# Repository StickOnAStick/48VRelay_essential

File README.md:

Ignore me trying to work with ki-cads git management. Project is located at `RelatBoard/48VRelay/48VERelay`

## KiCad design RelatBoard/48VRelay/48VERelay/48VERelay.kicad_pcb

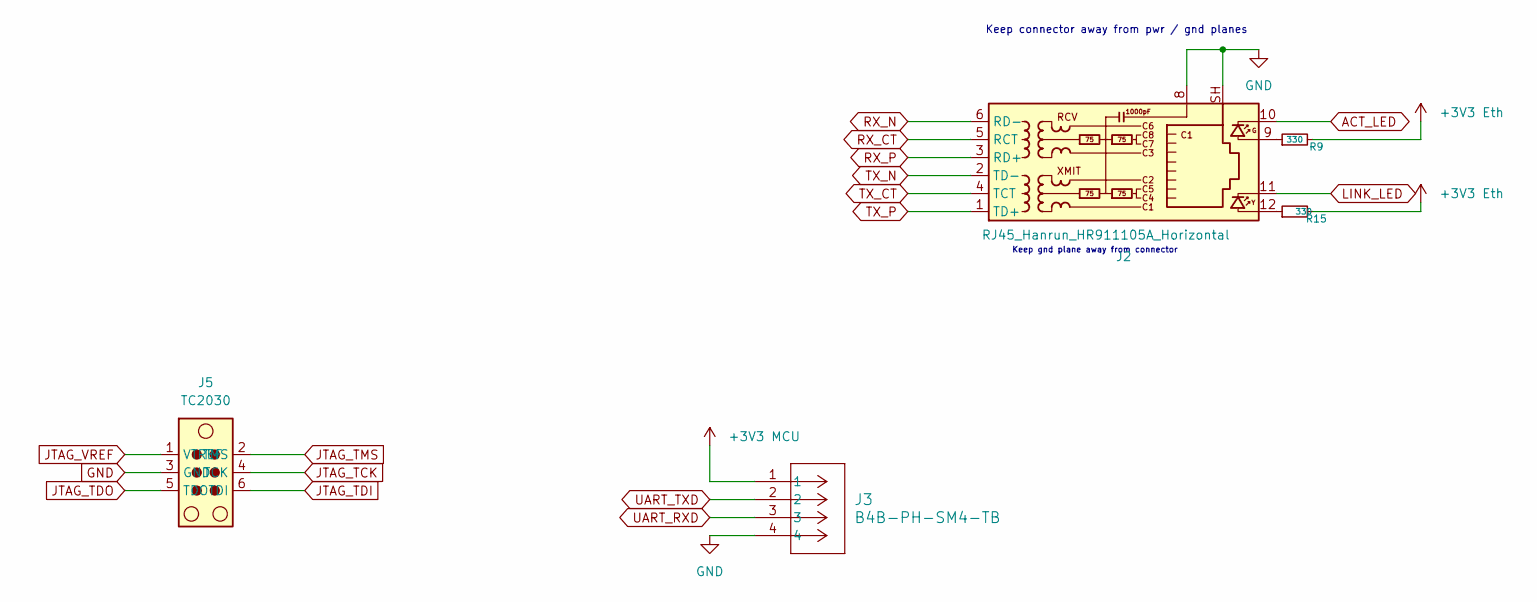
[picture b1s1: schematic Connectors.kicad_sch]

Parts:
J2: RJ45_Hanrun_HR911105A_Horizontal
J3: B4B-PH-SM4-TB; PinHeader_1x04_P2.54mm_Vertical
J5: TC2030; Tag-Connect_TC2030-IDC-NL_2x03_P1.27mm_Vertical
R9, R15: 330; R_0603_1608Metric

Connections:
3V3 MCU: J3.1; also elsewhere on the board
+3V3 Eth: R9.2, R15.2; also elsewhere on the board
ACT_LED: J2.10; also elsewhere on the board
GND: J2.8, J2.SH, J3.4; also elsewhere on the board
LINK_LED: J2.11; also elsewhere on the board
unnamed: J2.9, R9.1
unnamed: J2.12, R15.1
RX_CT: J2.5 (RCT); also elsewhere on the board
RX_N: J2.6 (RD-); also elsewhere on the board
RX_P: J2.3 (RD+); also elsewhere on the board
TX_CT: J2.4 (TCT); also elsewhere on the board
TX_N: J2.2 (TD-); also elsewhere on the board
TX_P: J2.1 (TD+); also elsewhere on the board
UART_RXD: J3.3; also elsewhere on the board
UART_TXD: J3.2; also elsewhere on the board

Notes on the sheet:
Keep gnd plane away from connector
Keep connector away from pwr / gnd planes

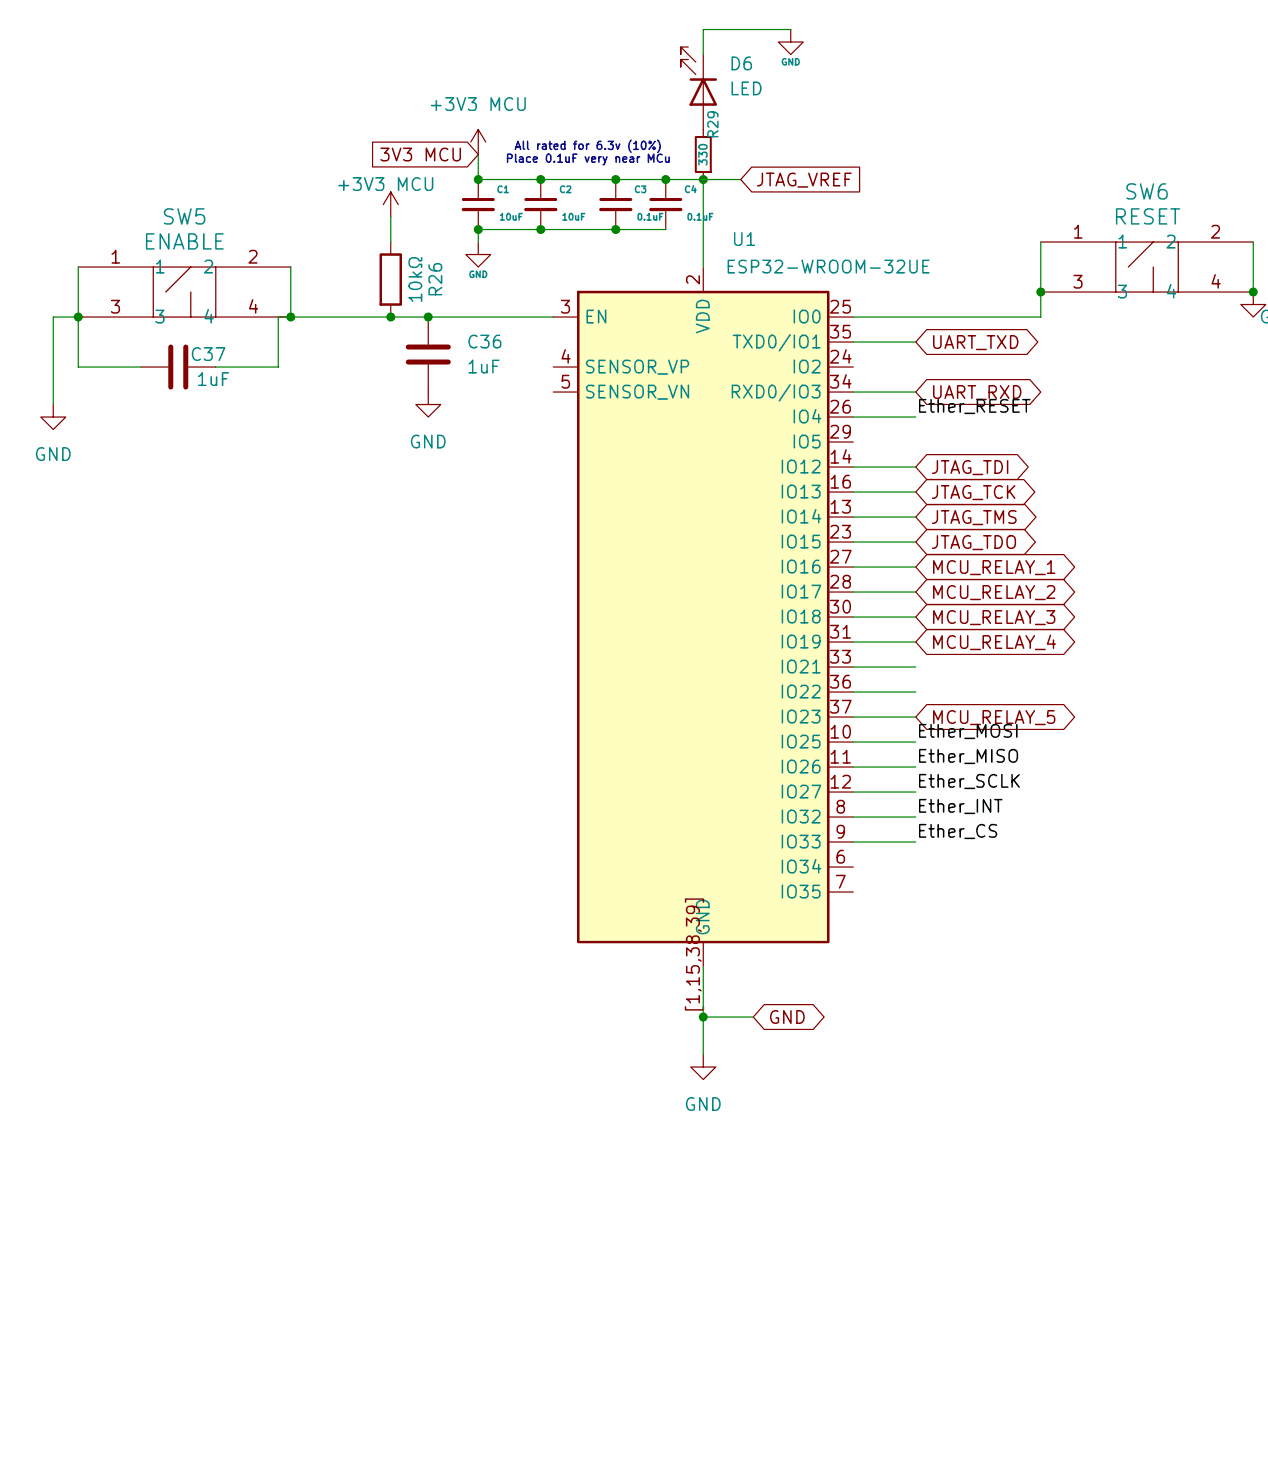
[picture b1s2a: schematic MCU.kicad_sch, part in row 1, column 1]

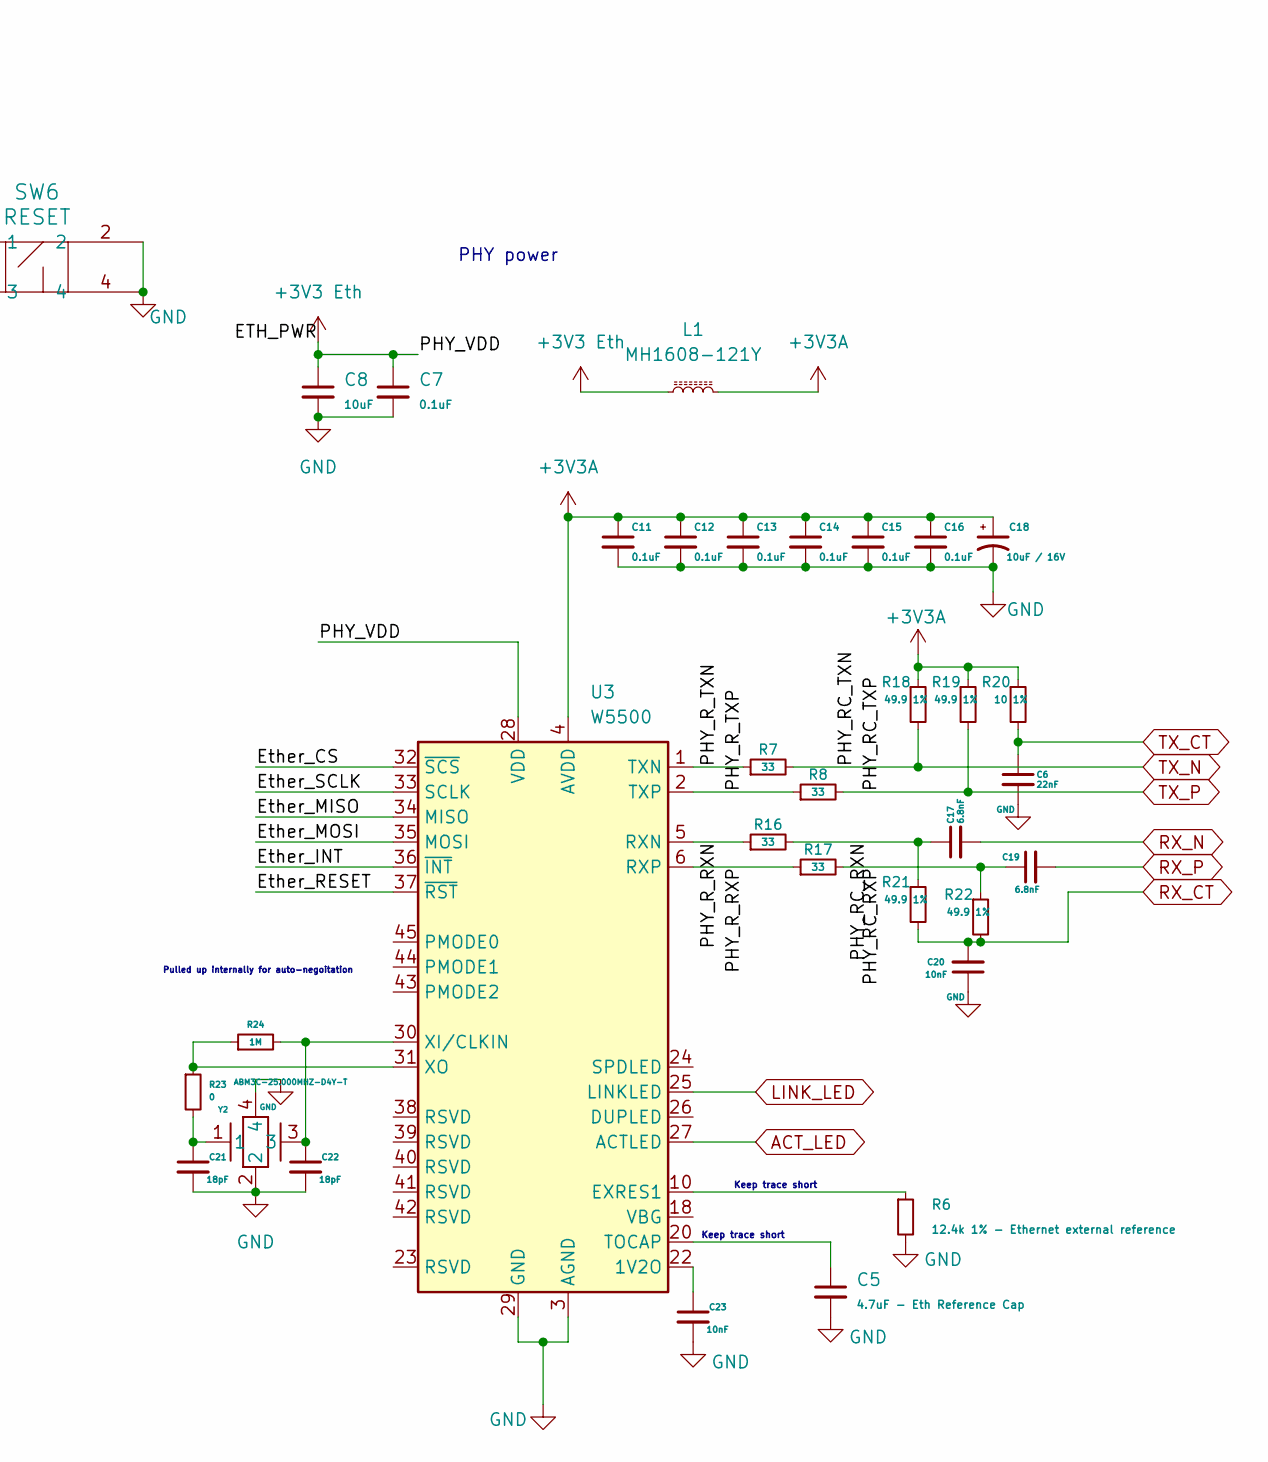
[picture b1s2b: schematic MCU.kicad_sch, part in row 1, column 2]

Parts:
C1, C8: 10uF; C_0805_2012Metric
C2: 10uF; C_0603_1608Metric
C3, C4: 0.1uF; C_0603_1608Metric
C5: 4.7uF - Eth Reference Cap; C_0201_0603Metric
C6: 22nF; C_0201_0603Metric
C7: 0.1uF; C_0201_0603Metric
C11, C12, C13, C14, C15, C16: 0.1uF; C_0402_1005Metric
C17, C19: 6.8nF; C_0201_0603Metric
C18: 10uF / 16V; C_0805_2012Metric
C20, C23: 10nF; C_0201_0603Metric
C21, C22: 18pF; C_0201_0603Metric
C36, C37: 1uF; C_0402_1005Metric
D6: LED; LED_0603_1608Metric
L1: MH1608-121Y; IND_BOURNS_MH1608
R6: 12.4k 1% - Ethernet external reference; R_0402_1005Metric
R7, R8, R16, R17: 33; R_0603_1608Metric
R18, R19, R21, R22: 49.9 1%; R_0201_0603Metric
R20: 10 1%; R_0201_0603Metric
R23: 0; R_0402_1005Metric
R24: 1M; R_0402_1005Metric
R26: 10kΩ; R_0402_1005Metric
R29: 330; R_0603_1608Metric
SW5: ENABLE; SW_PUSH_6mm_H5mm
SW6: RESET; SW_PUSH_6mm_H5mm
U1: ESP32-WROOM-32UE
U3: W5500; LQFP-48_7x7mm_P0.5mm
Y2: ABM3C-25.000MHZ-D4Y-T; Crystal_SMD_Abracon_ABM3C-4Pin_5.0x3.2mm

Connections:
3V3 MCU: C1.1, C2.1, C3.1, C4.1, R26.1, R29.1, U1.2 (VDD); also elsewhere on the board
+3V3 Eth: C7.1, C8.1, L1.1, U3.28 (VDD); also elsewhere on the board
+3V3A: C11.1, C12.1, C13.1, C14.1, C15.1, C16.1, C18.1, L1.2, R18.1, R19.1, R20.1, U3.4 (AVDD), U3.8 (AVDD), U3.11 (AVDD), U3.15 (AVDD), U3.17 (AVDD), U3.21 (AVDD); also elsewhere on the board
/MCU/Ether_CS: U1.9 (IO33), U3.32 (~SCS)
/MCU/Ether_INT: U1.8 (IO32), U3.36 (~INT)
/MCU/Ether_MISO: U1.11 (IO26), U3.34 (MISO)
/MCU/Ether_MOSI: U1.10 (IO25), U3.35 (MOSI)
/MCU/Ether_RESET: U1.26 (IO4), U3.37 (~RST)
/MCU/Ether_SCLK: U1.12 (IO27), U3.33 (SCLK)
/MCU/PHY_RC_RXN: C17.1, R16.2, R21.1
/MCU/PHY_RC_RXP: C19.1, R17.2, R22.1
/MCU/PHY_R_RXN: R16.1, U3.5 (RXN)
/MCU/PHY_R_RXP: R17.1, U3.6 (RXP)
/MCU/PHY_R_TXN: R7.1, U3.1 (TXN)
/MCU/PHY_R_TXP: R8.1, U3.2 (TXP)
ACT_LED: U3.27 (ACTLED); also elsewhere on the board
GND: C1.2, C2.2, C3.2, C4.2, C5.2, C6.2, C7.2, C8.2, C11.2, C12.2, C13.2, C14.2, C15.2, C16.2, C18.2, C20.1, C21.2, C22.2, C23.2, C36.2, C37.2, D6.1 (K), R6.2, SW5.1, SW5.3, SW6.2, SW6.4, U1.1 (GND), U1.15 (GND), U1.38 (GND), U1.39 (GND), U1.[1,15,38,39] (GND), U3.3 (AGND), U3.9 (AGND), U3.14 (AGND), U3.16 (AGND), U3.19 (AGND), U3.29 (GND), U3.48 (AGND), Y2.2, Y2.4; also elsewhere on the board
JTAG_TCK: U1.16 (IO13); also elsewhere on the board
JTAG_TDI: U1.14 (IO12); also elsewhere on the board
JTAG_TDO: U1.23 (IO15); also elsewhere on the board
JTAG_TMS: U1.13 (IO14); also elsewhere on the board
LINK_LED: U3.25 (LINKLED); also elsewhere on the board
MCU_RELAY_1: U1.27 (IO16); also elsewhere on the board
MCU_RELAY_2: U1.28 (IO17); also elsewhere on the board
MCU_RELAY_3: U1.30 (IO18); also elsewhere on the board
MCU_RELAY_4: U1.31 (IO19); also elsewhere on the board
MCU_RELAY_5: U1.37 (IO23); also elsewhere on the board
unnamed: C21.1, R23.2, Y2.1
unnamed: D6.2 (A), R29.2
unnamed: C36.1, C37.1, R26.2, SW5.2, SW5.4, U1.3 (EN)
unnamed: SW6.1, SW6.3, U1.25 (IO0)
unnamed: C23.1, U3.22 (1V2O)
unnamed: R6.1, U3.10 (EXRES1)
unnamed: C5.1, U3.20 (TOCAP)
unnamed: C22.1, R24.2, U3.30 (XI/CLKIN), Y2.3
unnamed: R23.1, R24.1, U3.31 (XO)
RX_CT: C20.2, R21.2, R22.2; also elsewhere on the board
RX_N: C17.2; also elsewhere on the board
RX_P: C19.2; also elsewhere on the board
TX_CT: C6.1, R20.2; also elsewhere on the board
TX_N: R7.2, R18.2; also elsewhere on the board
TX_P: R8.2, R19.2; also elsewhere on the board
UART_RXD: U1.34 (RXD0/IO3); also elsewhere on the board
UART_TXD: U1.35 (TXD0/IO1); also elsewhere on the board

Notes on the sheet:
Keep trace short
PHY power
All rated for 6.3v (10%) Place 0.1uF very near MCu
Pulled up internally for auto-negoitation

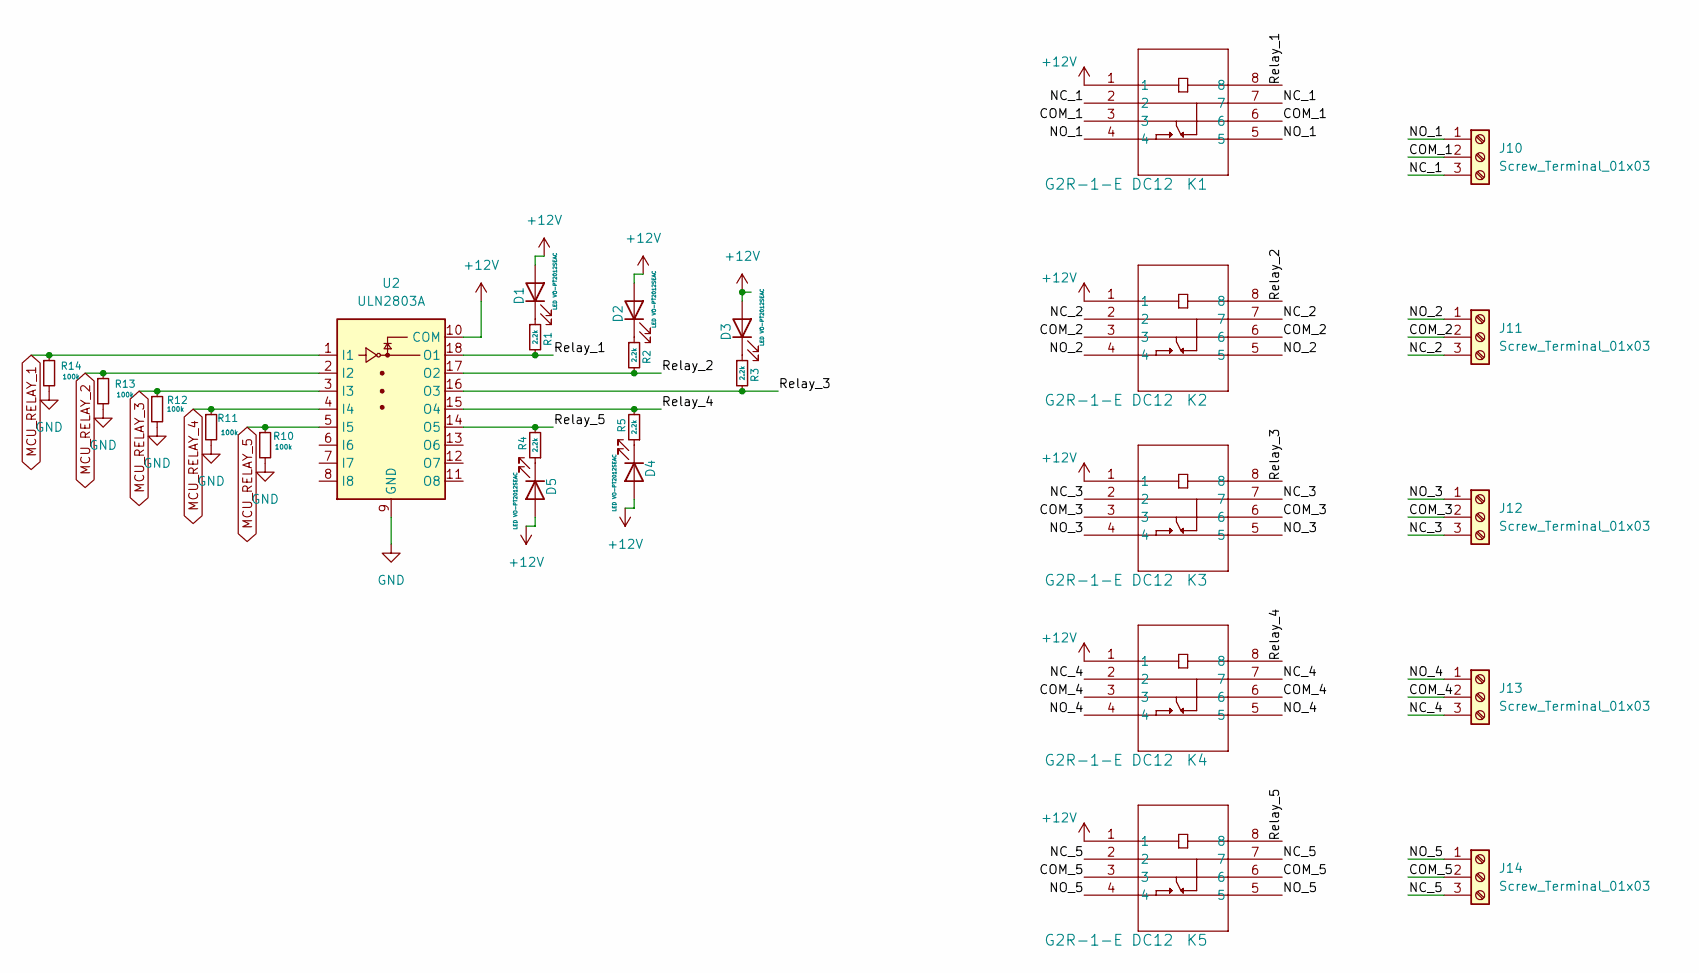
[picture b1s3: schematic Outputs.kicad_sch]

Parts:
D1, D2, D3, D4, D5: LED VO-PT2012SEAC; LED_0805_2012Metric
J10, J11, J12, J13, J14: Screw_Terminal_01x03; TerminalBlock_MaiXu_MX126-5.0-03P_1x03_P5.00mm
K1, K2, K3, K4, K5: G2R-1-E DC12; RELAY_G2R-1-E AC12_OMR
R1, R2, R3, R4, R5: 2.2k; R_0603_1608Metric
R10, R11, R12, R13, R14: 100k; R_0603_1608Metric
U2: ULN2803A; SOIC-18W_7.5x11.6mm_P1.27mm

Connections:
+12V: D1.2 (A), D2.2 (A), D3.2 (A), D4.2 (A), D5.2 (A), K1.1, K2.1, K3.1, K4.1, K5.1, U2.10 (COM); also elsewhere on the board
/Outputs/COM_1: J10.2, K1.3, K1.6; also elsewhere on the board
/Outputs/COM_2: J11.2, K2.3, K2.6; also elsewhere on the board
/Outputs/COM_3: J12.2, K3.3, K3.6; also elsewhere on the board
/Outputs/COM_4: J13.2, K4.3, K4.6; also elsewhere on the board
/Outputs/COM_5: J14.2, K5.3, K5.6; also elsewhere on the board
/Outputs/NC_1: J10.3, K1.2, K1.7; also elsewhere on the board
/Outputs/NC_2: J11.3, K2.2, K2.7; also elsewhere on the board
/Outputs/NC_3: J12.3, K3.2, K3.7; also elsewhere on the board
/Outputs/NC_4: J13.3, K4.2, K4.7; also elsewhere on the board
/Outputs/NC_5: J14.3, K5.2, K5.7; also elsewhere on the board
/Outputs/NO_1: J10.1, K1.4, K1.5; also elsewhere on the board
/Outputs/NO_2: J11.1, K2.4, K2.5; also elsewhere on the board
/Outputs/NO_3: J12.1, K3.4, K3.5; also elsewhere on the board
/Outputs/NO_4: J13.1, K4.4, K4.5; also elsewhere on the board
/Outputs/NO_5: J14.1, K5.4, K5.5; also elsewhere on the board
/Outputs/Relay_1: K1.8, R1.2, U2.18 (O1); also elsewhere on the board
/Outputs/Relay_2: K2.8, R2.2, U2.17 (O2); also elsewhere on the board
/Outputs/Relay_3: K3.8, R3.2, U2.16 (O3); also elsewhere on the board
/Outputs/Relay_4: K4.8, R5.2, U2.15 (O4); also elsewhere on the board
/Outputs/Relay_5: K5.8, R4.2, U2.14 (O5); also elsewhere on the board
GND: R10.2, R11.2, R12.2, R13.2, R14.2, U2.9 (GND); also elsewhere on the board
MCU_RELAY_1: R14.1, U2.1 (I1); also elsewhere on the board
MCU_RELAY_2: R13.1, U2.2 (I2); also elsewhere on the board
MCU_RELAY_3: R12.1, U2.3 (I3); also elsewhere on the board
MCU_RELAY_4: R11.1, U2.4 (I4); also elsewhere on the board
MCU_RELAY_5: R10.1, U2.5 (I5); also elsewhere on the board
unnamed: D1.1 (K), R1.1
unnamed: D2.1 (K), R2.1
unnamed: D3.1 (K), R3.1
unnamed: D4.1 (K), R5.1
unnamed: D5.1 (K), R4.1

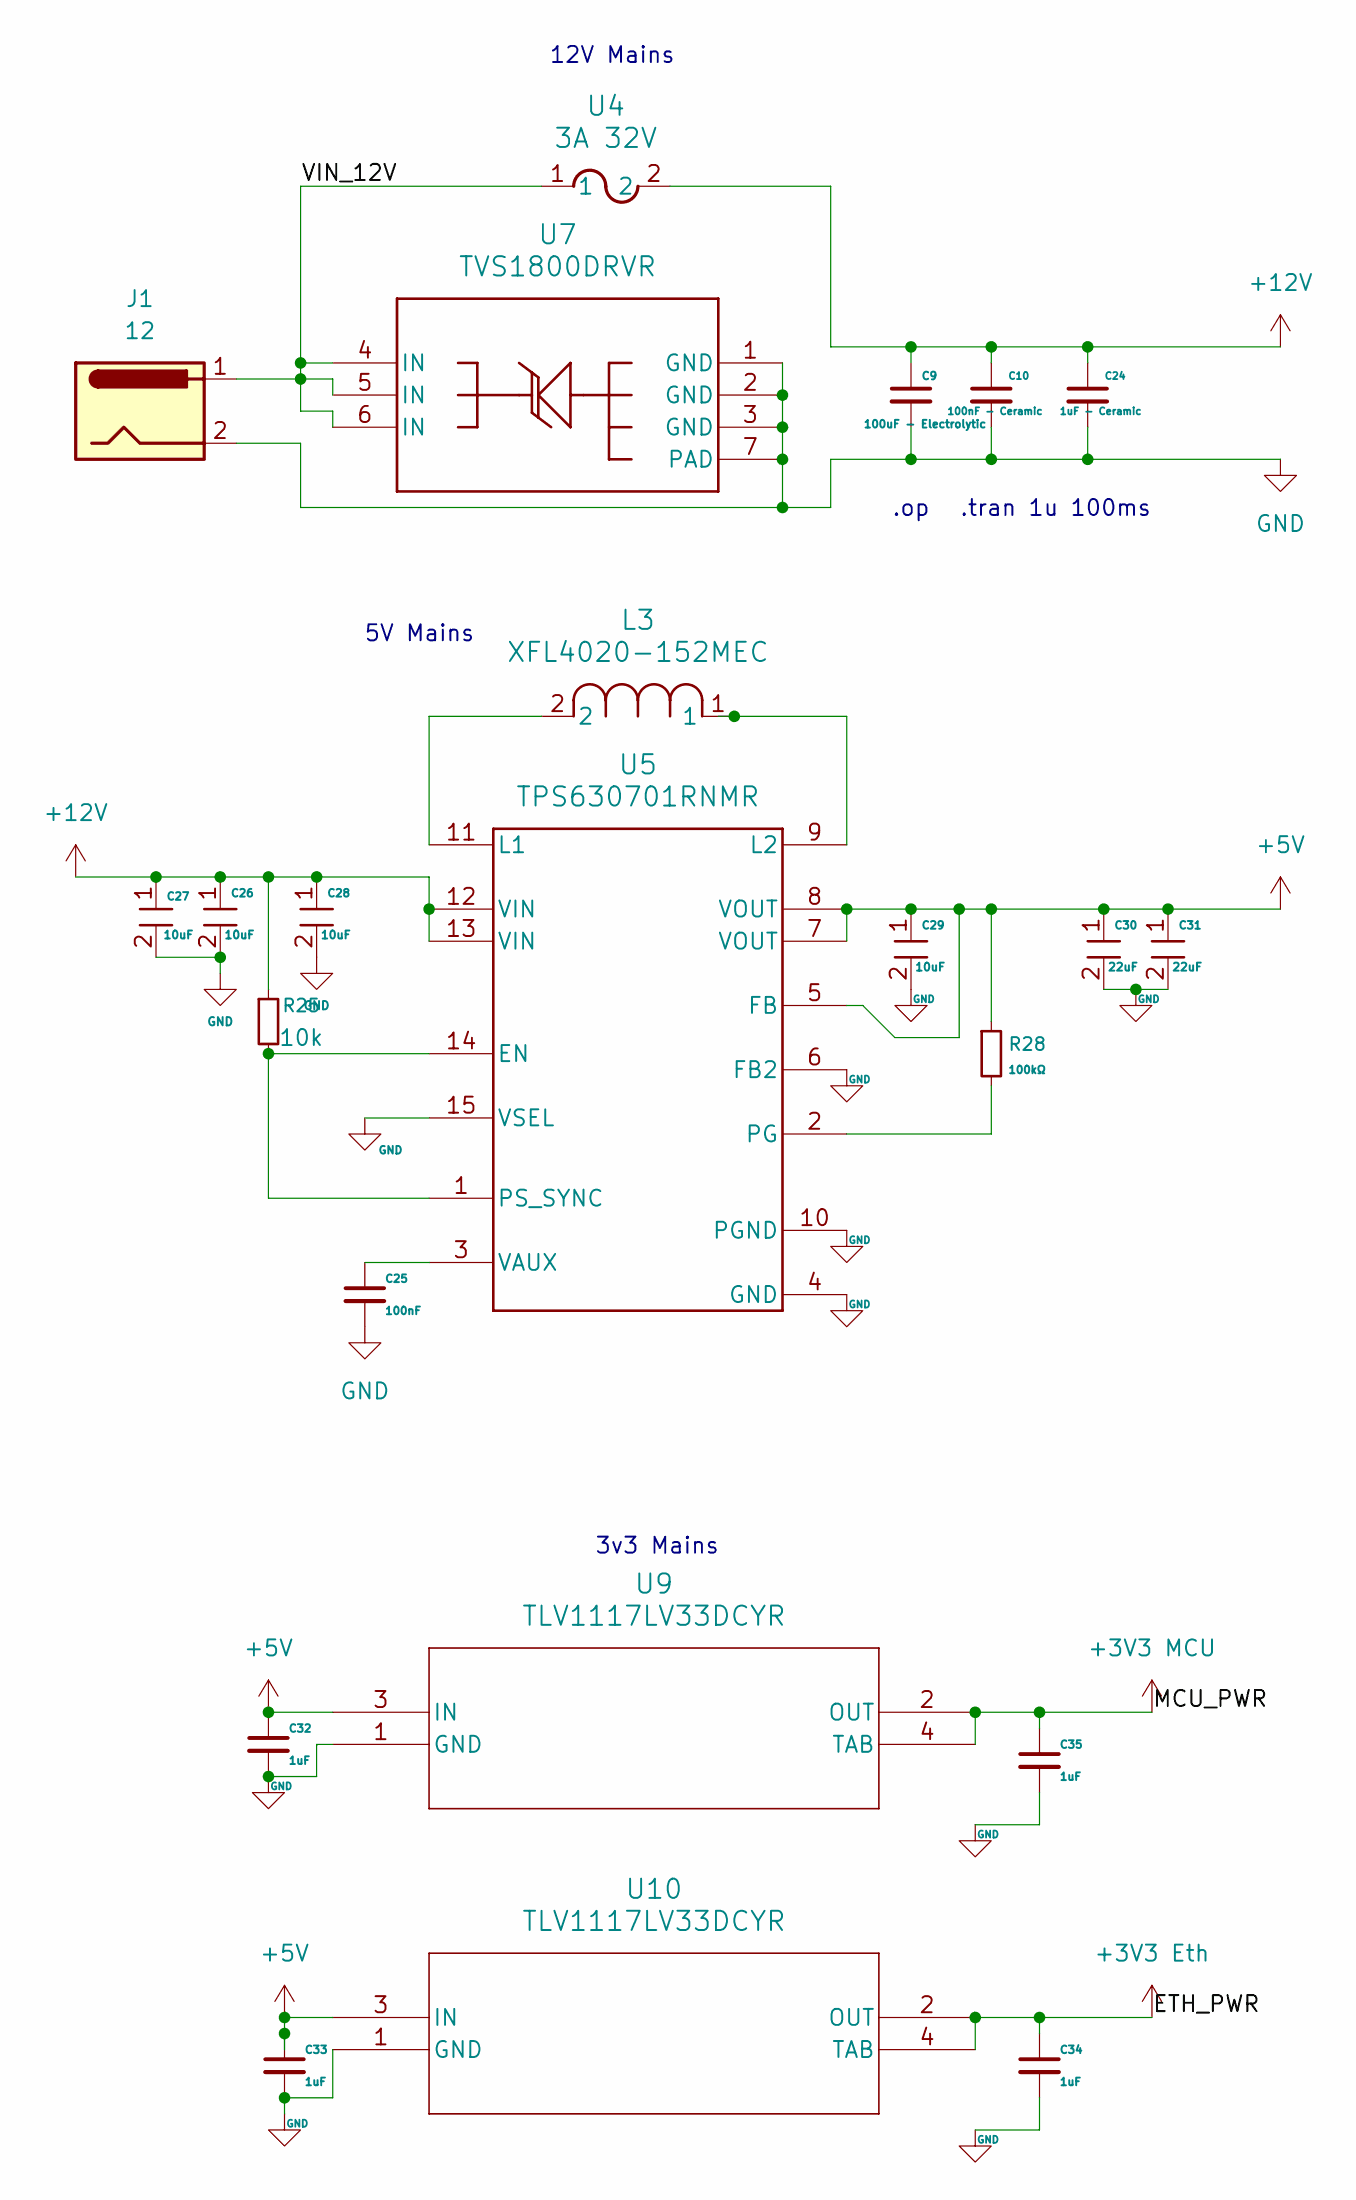
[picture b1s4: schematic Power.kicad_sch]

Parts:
C9: 100uF - Electrolytic; C_Elec_6.3x7.7
C10: 100nF - Ceramic; C_0201_0603Metric
C24: 1uF - Ceramic; C_0805_2012Metric
C25: 100nF; C_0201_0603Metric
C26, C27: 10uF; C_0805_2012Metric
C28, C29: 10uF; C_0603_1608Metric
C30, C31: 22uF; C_0805_2012Metric
C32, C33: 1uF; C_0201_0603Metric
C34, C35: 1uF; C_0805_2012Metric
J1: 12; BarrelJack_CUI_PJ-102AH_Horizontal
L3: XFL4020-152MEC; IND_XFL4020_COC-M
R25: 10k; R_0603_1608Metric
R28: 100kΩ; R_0603_1608Metric
U4: 3A 32V; Fuse_1206_3216Metric
U5: TPS630701RNMR; RNM0015A
U7: TVS1800DRVR; DRV0006A_NV
U9, U10: TLV1117LV33DCYR; TLV1117-33IDCYR

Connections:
3V3 MCU: C35.1, U9.2 (OUT), U9.4 (TAB); also elsewhere on the board
+3V3 Eth: C34.1, U10.2 (OUT), U10.4 (TAB); also elsewhere on the board
+5V: C29.1, C30.1, C31.1, C32.1, C33.1, R28.1, U5.5 (FB), U5.7 (VOUT), U5.8 (VOUT), U9.3 (IN), U10.3 (IN); also elsewhere on the board
+12V: C9.1, C10.1, C24.1, C26.1, C27.1, C28.1, R25.1, U4.2, U5.12 (VIN), U5.13 (VIN); also elsewhere on the board
/Power/VIN_12V: J1.1, U4.1, U7.4 (IN), U7.5 (IN), U7.6 (IN)
GND: C9.2, C10.2, C24.2, C25.2, C26.2, C27.2, C28.2, C29.2, C30.2, C31.2, C32.2, C33.2, C34.2, C35.2, J1.2, U5.4 (GND), U5.6 (FB2), U5.10 (PGND), U5.15 (VSEL), U7.1 (GND), U7.2 (GND), U7.3 (GND), U7.7 (PAD), U9.1 (GND), U10.1 (GND); also elsewhere on the board
unnamed: R25.2, U5.1 (PS_SYNC), U5.14 (EN)
unnamed: L3.2, U5.11 (L1)
unnamed: L3.1, U5.9 (L2)
unnamed: R28.2, U5.2 (PG)
unnamed: C25.1, U5.3 (VAUX)

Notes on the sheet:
3v3 Mains
12V Mains
5V Mains
.tran 1u 100ms
.op

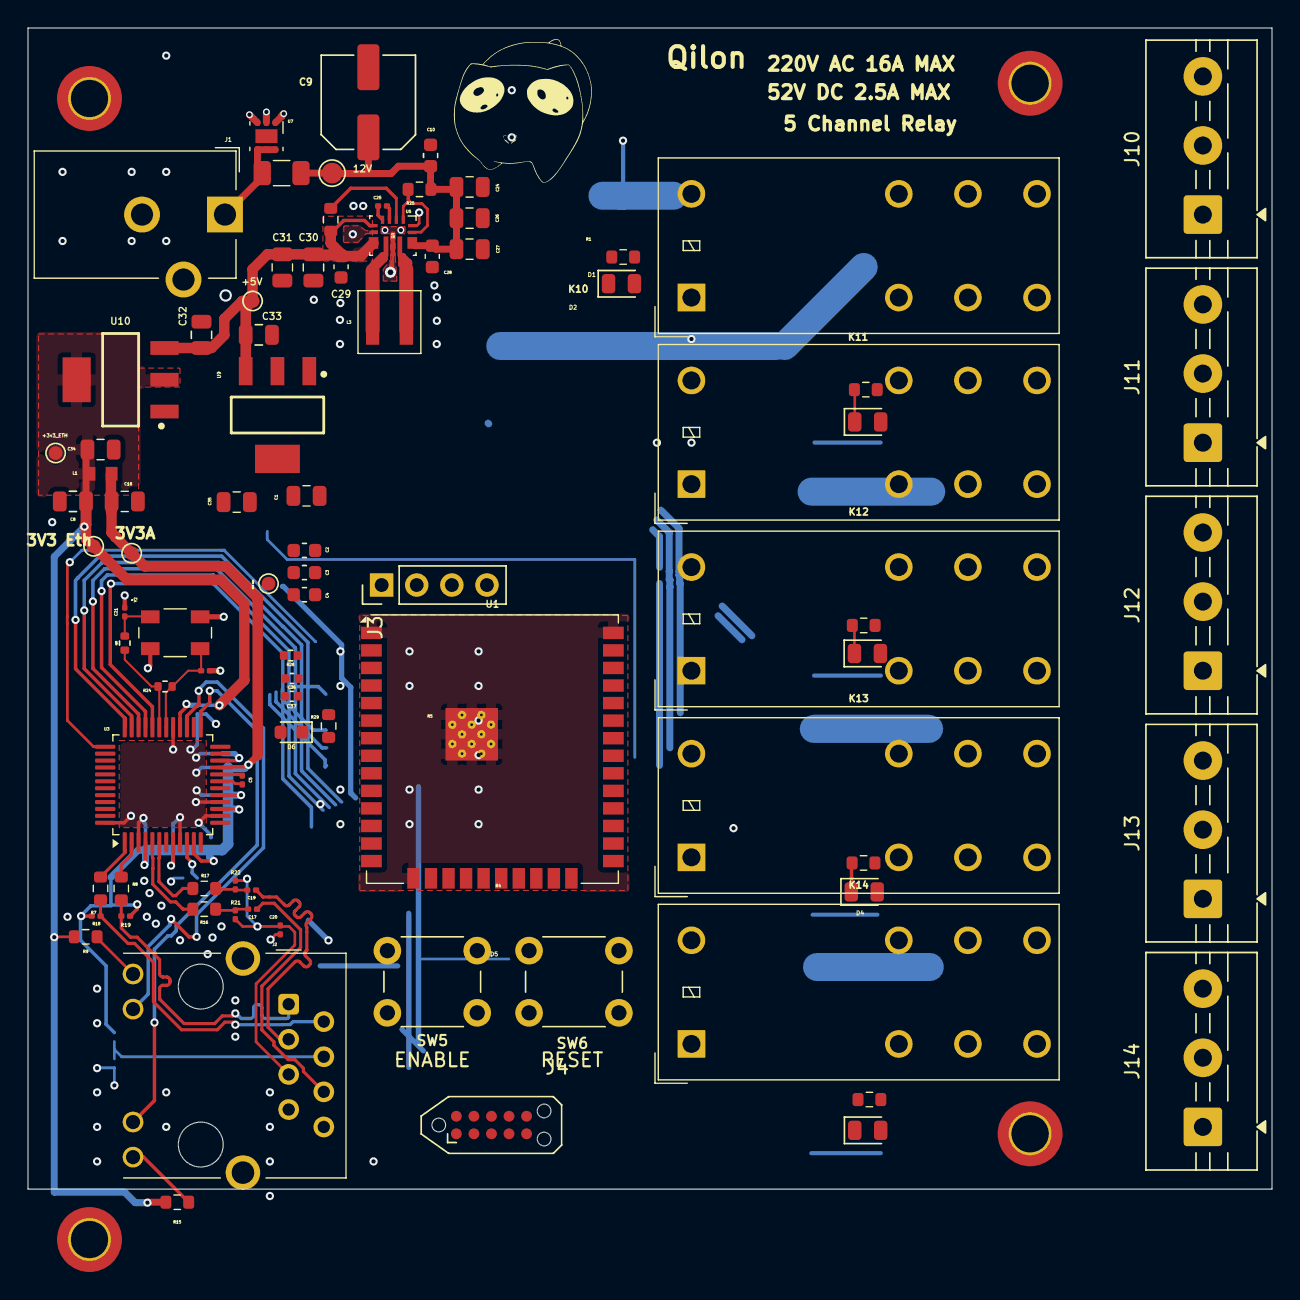
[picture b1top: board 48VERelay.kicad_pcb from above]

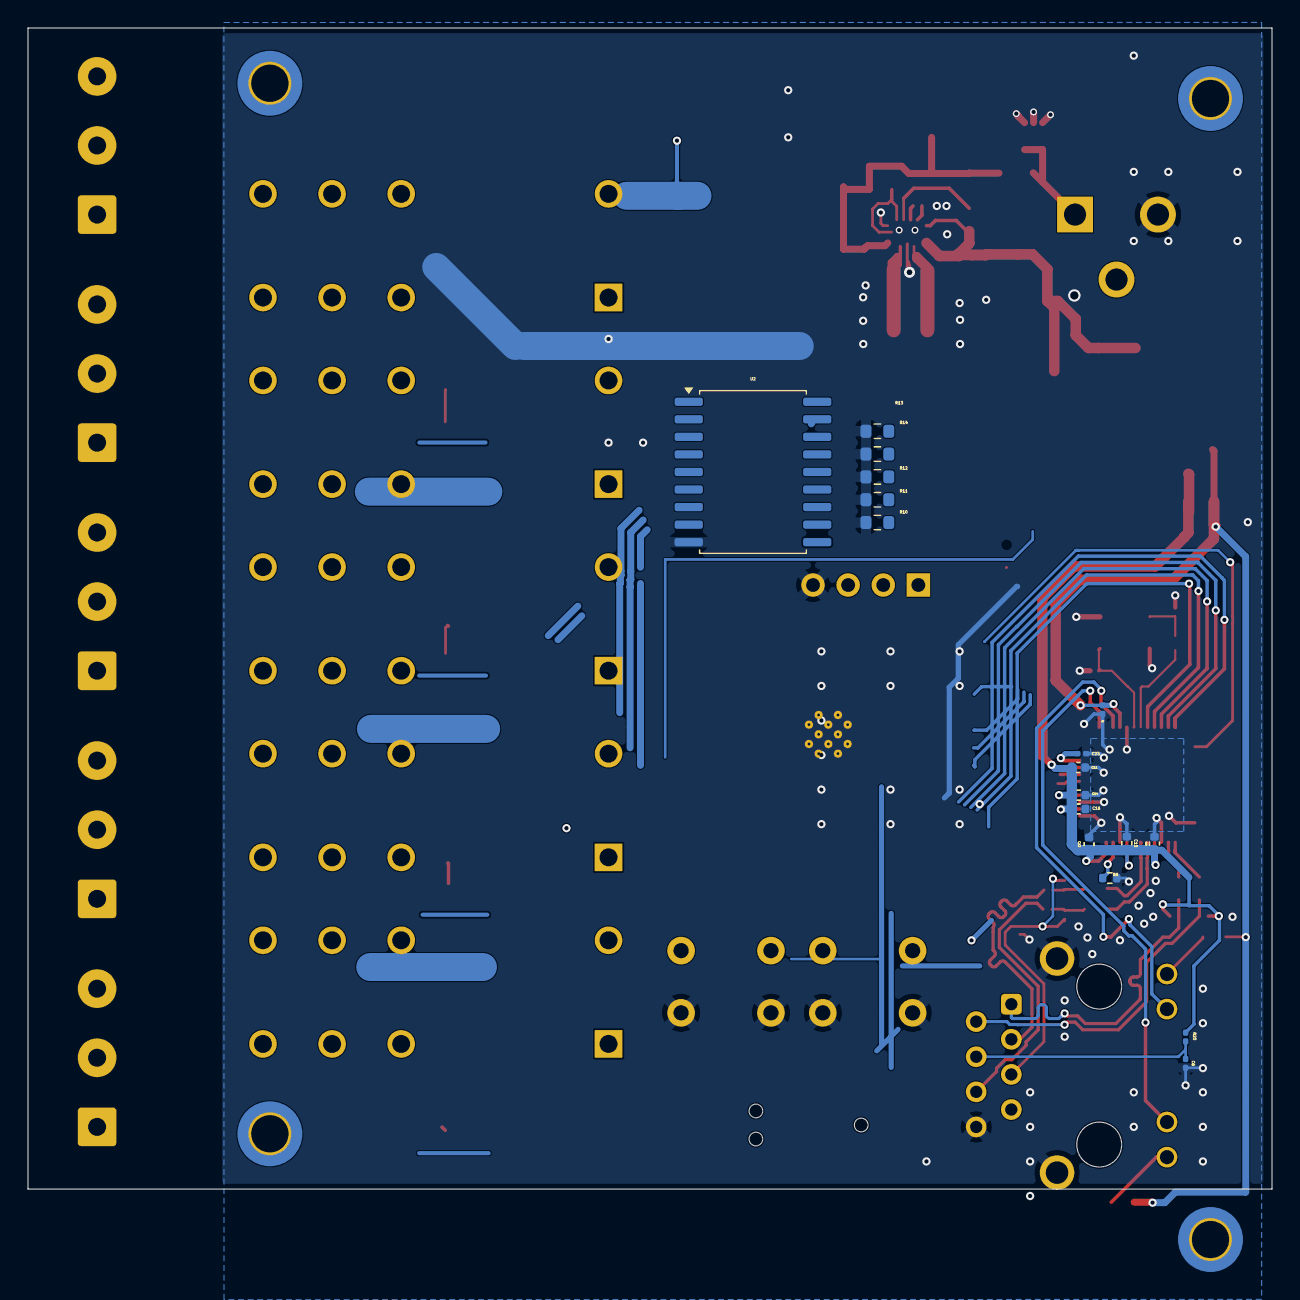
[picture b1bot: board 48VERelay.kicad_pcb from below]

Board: 4 copper layers, 90.0 x 84.0 mm, 104 parts (17 on the bottom side), 79 nets.

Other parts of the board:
3V3 Eth, 3V3 MCU, 3V3A: TestPoint_Pad_D1.0mm
12V: TestPoint_Pad_D1.5mm
+3v3_ETH, +5V: TestPoint_Pad_D1.0mm
J4: TC2050; Tag-Connect_TC2050-IDC-NL_2x05_P1.27mm_Vertical
K10, K11, K12, K13, K14: G2RL-1-E; Relay_SPDT_Omron_G2RL-1-E

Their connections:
3V3 MCU: 3V3 MCU.1, J4.1; also elsewhere on the board
+3V3 Eth: 3V3 Eth.1, +3v3_ETH.1; also elsewhere on the board
+3V3A: 3V3A.1; also elsewhere on the board
+5V: +5V.1; also elsewhere on the board
+12V: 12V.1, K10.A1, K11.A1, K12.A1, K13.A1, K14.A1; also elsewhere on the board
/Outputs/COM_1: K10.11; also elsewhere on the board
/Outputs/COM_2: K11.11; also elsewhere on the board
/Outputs/COM_3: K12.11; also elsewhere on the board
/Outputs/COM_4: K13.11; also elsewhere on the board
/Outputs/COM_5: K14.11; also elsewhere on the board
/Outputs/NC_1: K10.12; also elsewhere on the board
/Outputs/NC_2: K11.12; also elsewhere on the board
/Outputs/NC_3: K12.12; also elsewhere on the board
/Outputs/NC_4: K13.12; also elsewhere on the board
/Outputs/NC_5: K14.12; also elsewhere on the board
/Outputs/NO_1: K10.14; also elsewhere on the board
/Outputs/NO_2: K11.14; also elsewhere on the board
/Outputs/NO_3: K12.14; also elsewhere on the board
/Outputs/NO_4: K13.14; also elsewhere on the board
/Outputs/NO_5: K14.14; also elsewhere on the board
/Outputs/Relay_1: K10.A2; also elsewhere on the board
/Outputs/Relay_2: K11.A2; also elsewhere on the board
/Outputs/Relay_3: K12.A2; also elsewhere on the board
/Outputs/Relay_4: K13.A2; also elsewhere on the board
/Outputs/Relay_5: K14.A2; also elsewhere on the board
GND: J4.2, J4.3, J4.4, J4.5; also elsewhere on the board
JTAG_TCK: J4.9; also elsewhere on the board
JTAG_TDI: J4.7; also elsewhere on the board
JTAG_TDO: J4.8; also elsewhere on the board
JTAG_TMS: J4.10; also elsewhere on the board

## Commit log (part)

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2026-06-15 Start Sim
2026-06-15 sys_update
2026-06-17 begin pcb design
2026-06-22 Begin PCB layout
2026-06-27 5v5 Buck Added
2026-06-29 Fix 12V->5V add power plane
